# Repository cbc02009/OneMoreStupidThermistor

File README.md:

# OneMoreStupidThermistor

For when you need just one (or two) more stupid thermistor ports on your printer. This board takes an MCU of the Xiao or adafruit QT PY formfactor

# Images

# Seeduino Xiao Config Example
```ini
[mcu jomt]
serial: /dev/serial/by-id/usb-Klipper_samd21g18a_F6407A985733535020312E322A090CFF-if00
restart_method: command

#If using T1
[temperature_sensor chamber]
sensor_type: Generic 3950
sensor_pin: jomt:PA2

#If using T2
[temperature_sensor chamber]
sensor_type: Generic 3950
sensor_pin: jomt:PA5
```

# Adafruit QT Py rp2040 Config Example
```ini
[mcu jomt]
serial: /dev/serial/by-id/usb-Klipper_rp2040_DF60BCA003201A39-if00
restart_method: command

#If using T1
[temperature_sensor chamber]
sensor_type: Generic 3950
sensor_pin: jomt:gpio28

#If using T2
[temperature_sensor chamber]
sensor_type: Generic 3950
sensor_pin: jomt:gpio29
```

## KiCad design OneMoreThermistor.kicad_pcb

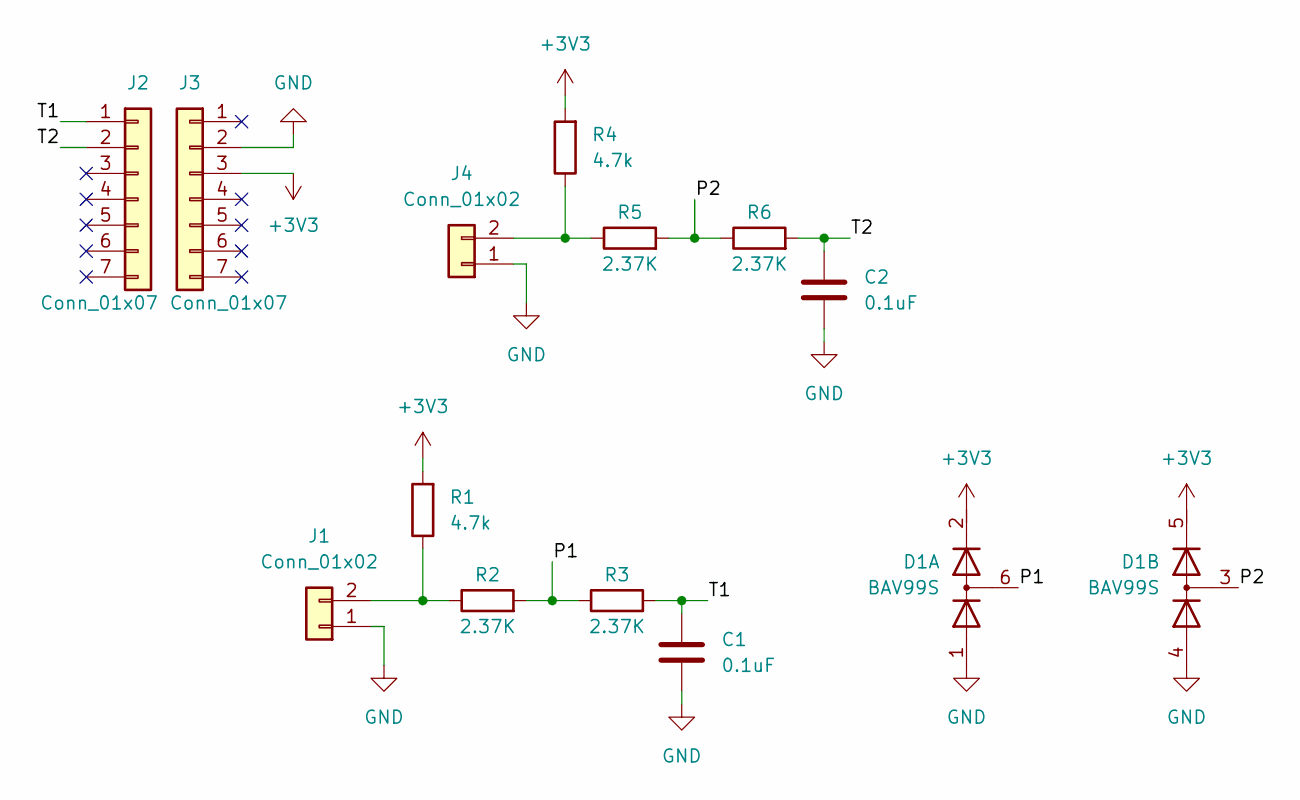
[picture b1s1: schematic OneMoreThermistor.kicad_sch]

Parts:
C1, C2: 0.1uF; C_0805_2012Metric
D1: BAV99S; SOT-363_SC-70-6
J1, J4: Conn_01x02; JST_XH_B2B-XH-A_1x02_P2.50mm_Vertical
J2, J3: Conn_01x07; PinHeader_1x07_P2.54mm_Vertical
R1, R4: 4.7k; R_0805_2012Metric
R2, R3, R5, R6: 2.37K; R_0805_2012Metric

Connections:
+3V3: D1.2 (K2), D1.5 (K4), J3.3, R1.2, R4.2
/P1: D1.6 (K3A4), R2.2, R3.1
/P2: D1.3 (K1A2), R5.2, R6.1
/T1: C1.1, J2.1, R3.2
/T2: C2.1, J2.2, R6.2
GND: C1.2, C2.2, D1.1 (A1), D1.4 (A3), J1.1, J3.2, J4.1
unnamed: J1.2, R1.1, R2.1
unnamed: J4.2, R4.1, R5.1

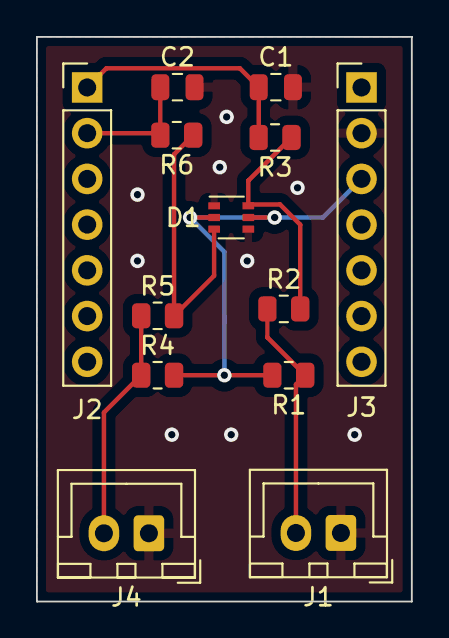
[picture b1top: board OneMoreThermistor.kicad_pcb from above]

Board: 2 copper layers, 20.8 x 31.4 mm, 13 parts (0 on the bottom side), 8 nets.

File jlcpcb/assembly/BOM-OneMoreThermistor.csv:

Comment,Designator,Footprint,LCSC
Conn_01x07,"J2,J3",PinHeader_1x07_P2.54mm_Vertical,C124418
0.1uF,"C1,C2",C_0805_2012Metric,C1525
Conn_01x02,"J1,J4",JST_XH_B2B-XH-A_1x02_P2.50mm_Vertical,C158012
2.37K,"R2,R3,R5,R6",R_0805_2012Metric,C17523
4.7k,"R1,R4",R_0805_2012Metric,C64354
BAV99S,D1,SOT-363_SC-70-6,C96225

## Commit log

2022-05-19 initial file commit
2022-05-19 Update gitignore.
2022-06-12 Include example for seeduino Xiao
2022-06-12 fix xiao example. add qt py 2040 example.
